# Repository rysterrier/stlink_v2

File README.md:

# stlink_v2
ST Link V2-1 Programmer project.

Small STLink V2 SW programmer clone.

This will project includes:
  Schematic of the programmer
  PCB file

Software used for this project:
  KiCad
  TopoR Autorouter

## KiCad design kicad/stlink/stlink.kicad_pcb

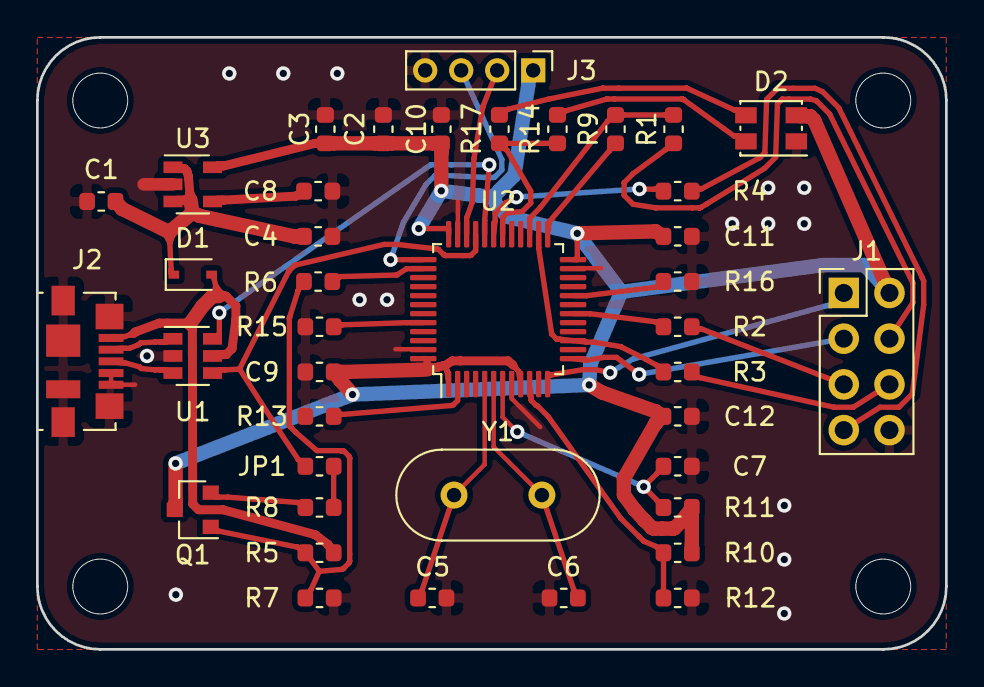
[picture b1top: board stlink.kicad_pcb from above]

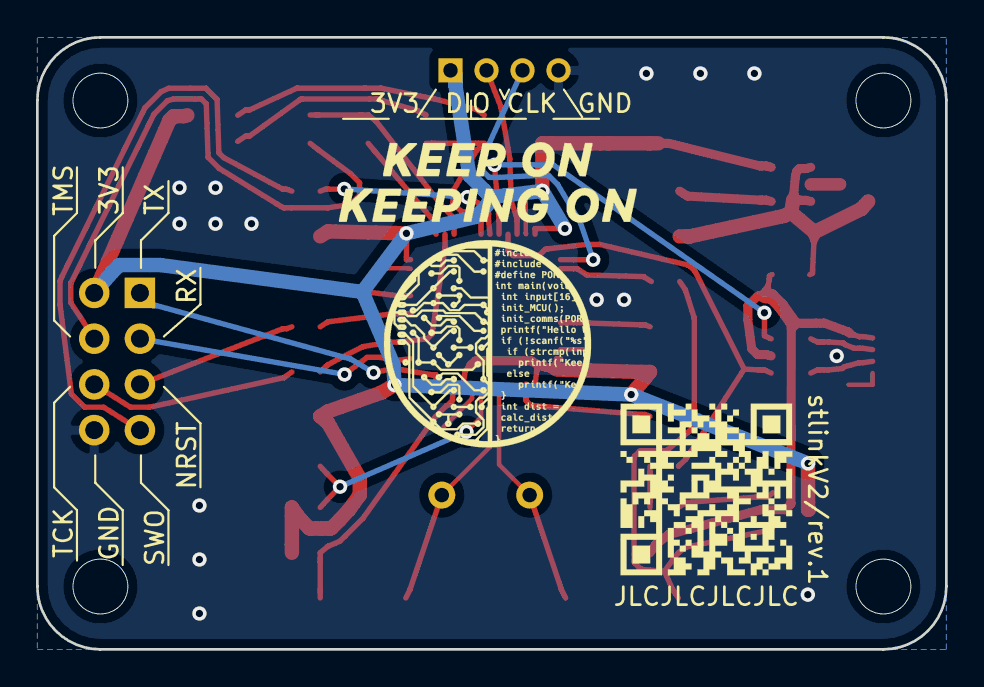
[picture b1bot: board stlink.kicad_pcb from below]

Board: 2 copper layers, 50.5 x 34.0 mm, 42 parts (2 on the bottom side), 36 nets.

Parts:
C1, C2, C9: 1uF; C_0603_1608Metric
C3, C4, C7, C10, C11, C12: 100nF; C_0603_1608Metric
C5, C6: 22pF; C_0603_1608Metric
C8: 10nF; C_0603_1608Metric
D1: BAT60A; D_SOD-323
D2: AAA3528; LED_Kingbright_AAA3528ESGCT
G1: LOGO; qr_stlink_v2
G2: LOGO; keep_on
J1: DEBUG; PinHeader_2x04_P2.54mm_Vertical
J2: USB_Micro; USB_Micro-B_Molex_47346-0001
J3: MCU_FLASHING; PinHeader_1x04_P2.00mm_Vertical
JP1: Solder bridge; R_0603_1608Metric
Q1: KTC9013S; SOT-23
R1, R2, R3, R4, R6: 22; R_0603_1608Metric
R5, R13: 10k; R_0603_1608Metric
R7: 36k; R_0603_1608Metric
R8: 1k5; R_0603_1608Metric
R9, R14, R17: 100; R_0603_1608Metric
R10, R11, R12, R15, R16: 100k; R_0603_1608Metric
U1: USBLC6-2SC6; SOT-23-6
U2: STM32F103CBTx; LQFP-48_7x7mm_P0.5mm
U3: LD3985M33R_SOT23; SOT-23-5
Y1: Crystal; Crystal_HC49-U_Vertical

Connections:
+3V3: C2.1, C3.1, C9.1, C10.1, C11.1, C12.1, D2.4, J1.2, J3.1, Q1.3, R10.2, R11.2, U2.1, U2.9, U2.24, U2.36, U2.48, U3.5
+5V: D1.2, J2.1, R5.2, U1.5
/BOOT0: R15.2, U2.44
/BOOT1: R16.2, U2.20
/D+: J2.3, U1.3
/D-: J2.2, U1.1
/LED: R14.1, R17.2, U2.30
/NRST: C7.1, R11.1, U2.7
/OSC_IN: C5.1, U2.5, Y1.1
/OSC_OUT: C6.1, U2.6, Y1.2
/PC13: R13.2, U2.2
/RX: J1.3, U2.13
/SWCLK: J3.3, U2.37
/SWDIO: J3.2, U2.34
/TX: J1.1, U2.12
/T_JTCK: R3.2, U2.15, U2.26
/T_JTMS: R1.2, R9.1, U2.27
/T_NRST: R2.2, U2.18
/T_SWDIO_IN: R9.2, U2.25
/T_SWO: R4.2, U2.31
/USB_DM: U1.6, U2.32
/USB_DP: JP1.1, U1.4, U2.33
/USB_REN: R6.2, U2.38
/WAKEUP: R10.1, R12.2, U2.10
GND: C1.2, C2.2, C3.2, C4.2, C5.2, C6.2, C7.2, C8.2, C9.2, C10.2, C11.2, C12.2, D2.1, J1.8, J2.4, J2.5, J2.6, J3.4, R7.1, R12.1, R13.1, R15.1, R16.1, U1.2, U2.8, U2.23, U2.35, U2.47, U3.2
unnamed: C1.1, C4.1, D1.1, U3.1, U3.3
unnamed: C8.1, U3.4
unnamed: D2.2, R14.2
unnamed: D2.3, R17.1
unnamed: J1.4, R1.1
unnamed: J1.5, R2.1
unnamed: J1.6, R3.1
unnamed: J1.7, R4.1
unnamed: JP1.2, R8.1
unnamed: Q1.1, R5.1, R6.1, R7.2
unnamed: Q1.2, R8.2

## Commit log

2020-05-18 PCB+SCH commit
    Added scheme, PCB and BOM files.
2020-05-22 sch + pcb update
    Updated schematics:
    * Added ESD protection for USB
    * Added notes and comments to schematics
    * Added BOM
    Updated PCB:
    * Slightly changed layout
